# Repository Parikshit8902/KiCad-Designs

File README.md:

# KiCad-Designs
Here's some of my design prototypes, which I designed with the help of KiCad.
These designs have a schematic file as well as a PCB-Design file.

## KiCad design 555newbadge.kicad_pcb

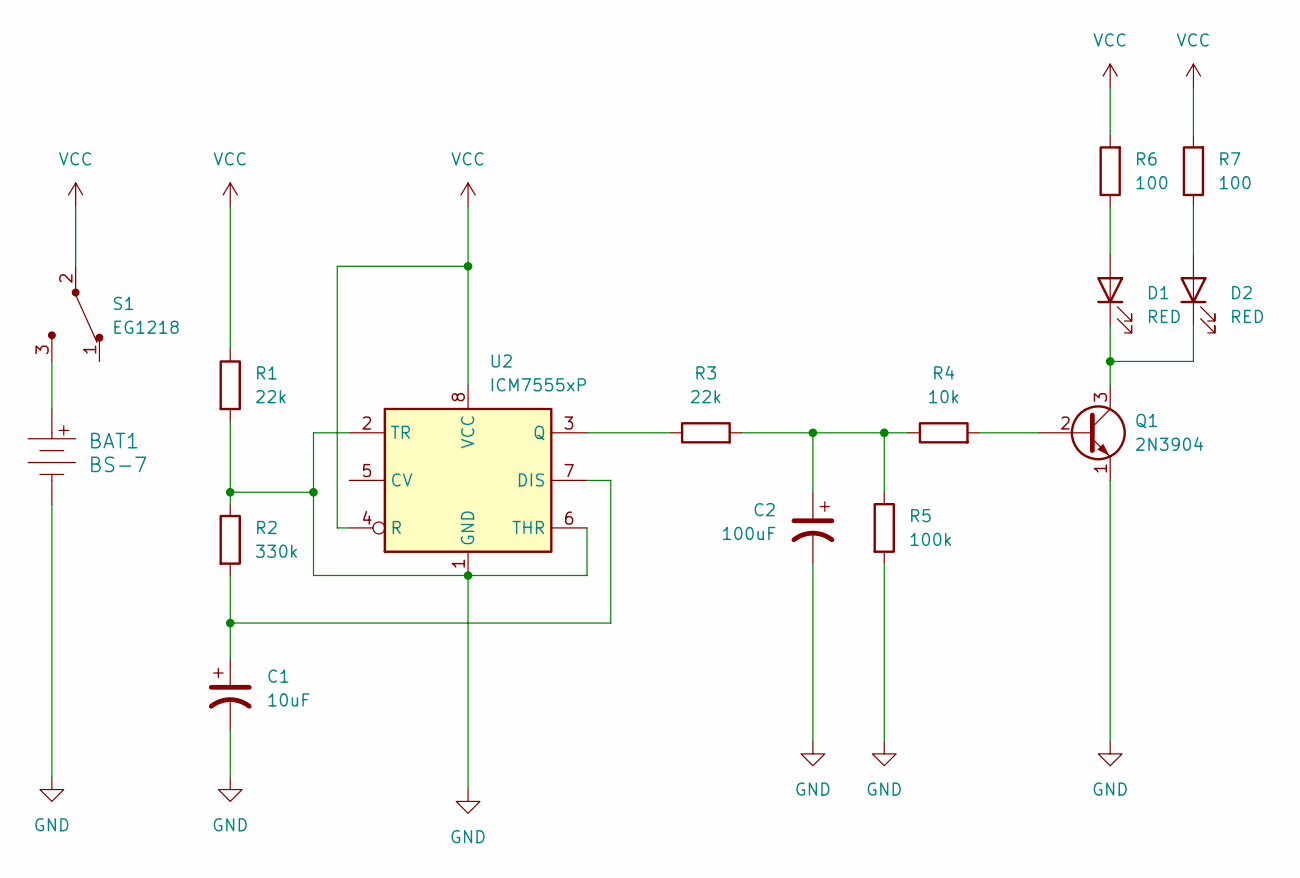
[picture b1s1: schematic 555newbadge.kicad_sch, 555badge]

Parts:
BAT1: BS-7; Battery_Holder_Coin_2032_BS-7; MPN BS-7; Digi-Key_PN BS-7-ND
C1: 10uF; CP_Radial_D5.0mm_P2.00mm
C2: 100uF; CP_Radial_D6.3mm_P2.50mm
D1, D2: RED; LED_D3.0mm
Q1: 2N3904; TO-92-3
R1, R3: 22k; R_Axial_DIN0207_L6.3mm_D2.5mm_P7.62mm_Horizontal
R2: 330k; R_Axial_DIN0207_L6.3mm_D2.5mm_P7.62mm_Horizontal
R4: 10k; R_Axial_DIN0207_L6.3mm_D2.5mm_P7.62mm_Horizontal
R5: 100k; R_Axial_DIN0207_L6.3mm_D2.5mm_P7.62mm_Horizontal
R6, R7: 100; R_Axial_DIN0207_L6.3mm_D2.5mm_P7.62mm_Horizontal
S1: EG1218; Switch_Slide_11.6x4mm_EG1218; MPN EG1218; Digi-Key_PN EG1903-ND
U2: ICM7555xP; DIP-8_W7.62mm

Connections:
GND: BAT1.Neg, C1.2, C2.2, Q1.1 (E), R1.2, R2.1, R5.2, U2.1 (GND), U2.2 (TR), U2.6 (THR)
unnamed: BAT1.Pos, S1.3
unnamed: C2.1, R3.2, R4.1, R5.1
unnamed: D1.2 (A), R6.1
unnamed: D1.1 (K), D2.1 (K), Q1.3 (C)
unnamed: D2.2 (A), R7.1
unnamed: Q1.2 (B), R4.2
unnamed: C1.1, R2.2, U2.7 (DIS)
unnamed: R3.1, U2.3 (Q)
VCC: R1.1, R6.2, R7.2, S1.2, U2.4 (R), U2.8 (VCC)

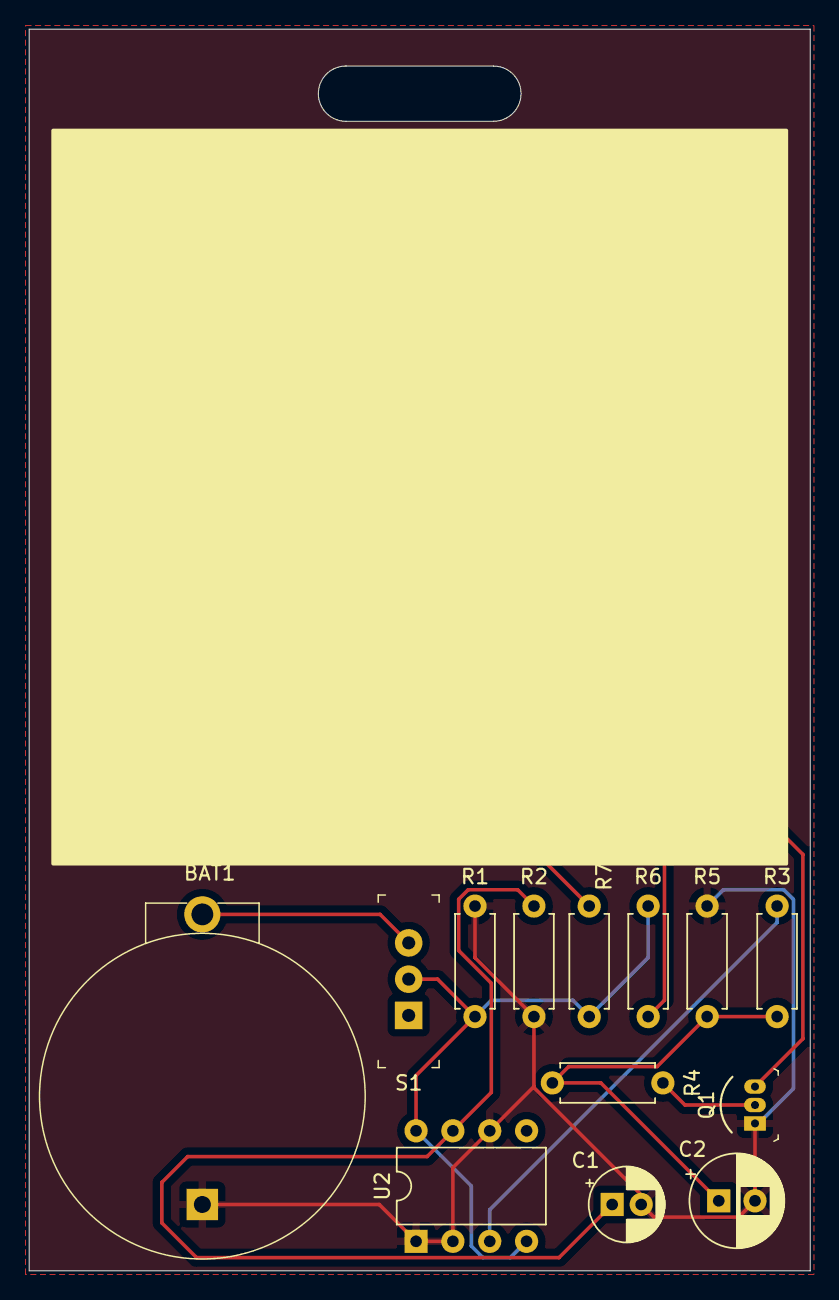
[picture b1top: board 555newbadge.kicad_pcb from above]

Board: 2 copper layers, 53.8 x 85.6 mm, 15 parts (0 on the bottom side), 10 nets.

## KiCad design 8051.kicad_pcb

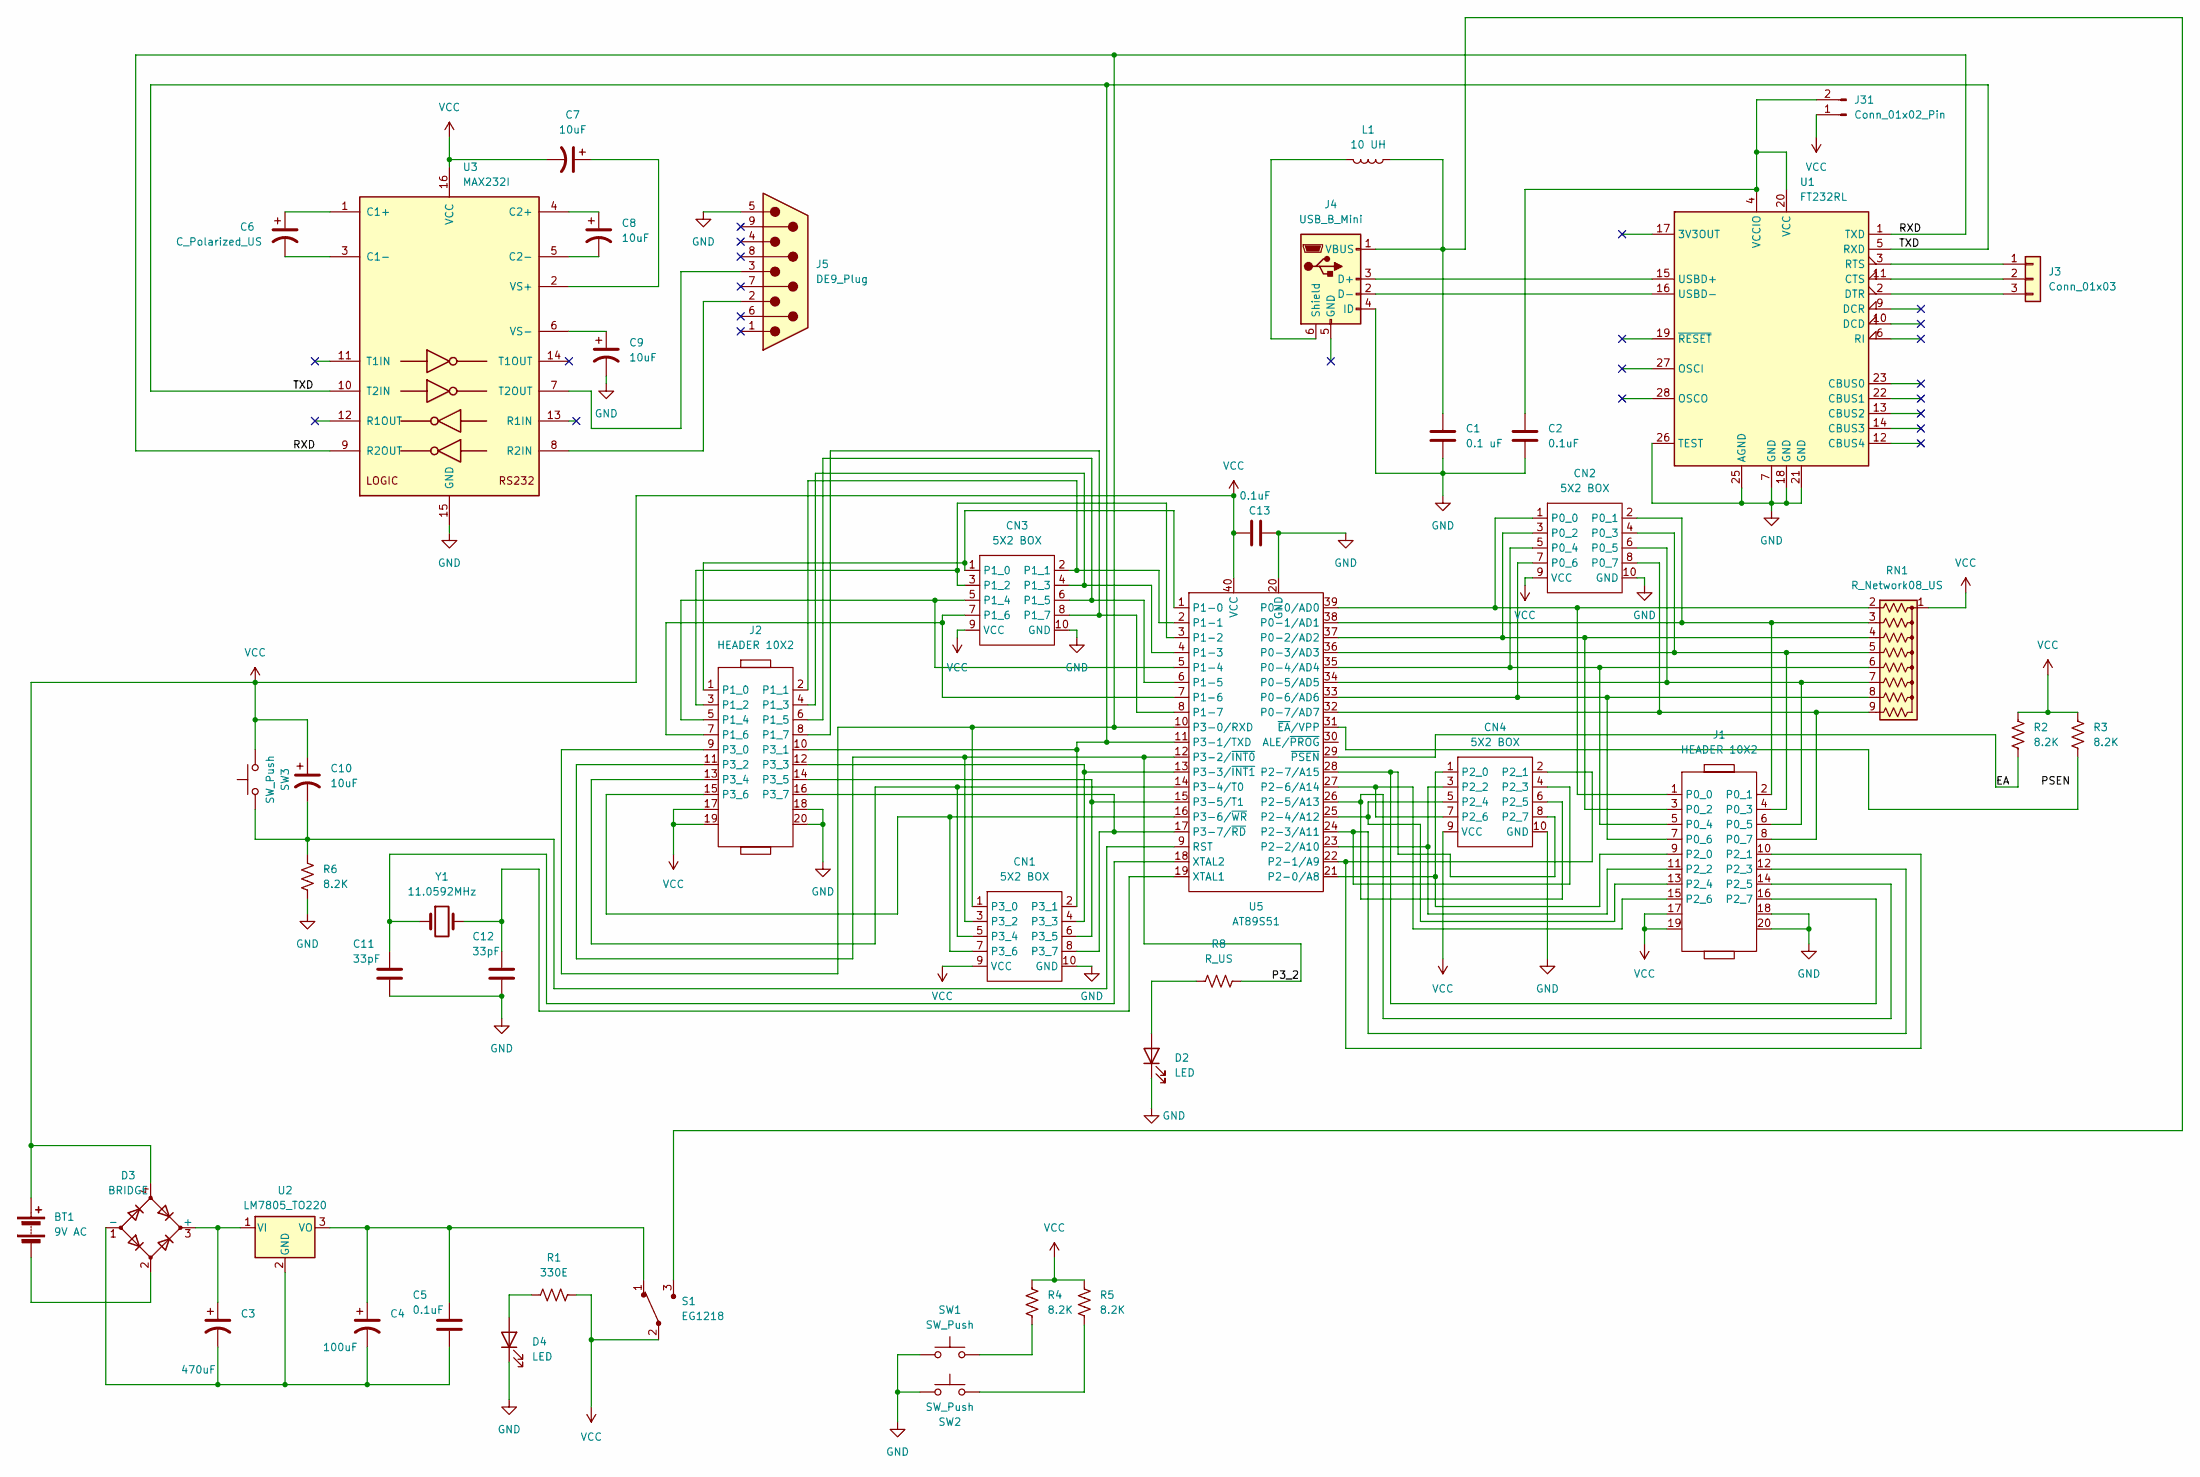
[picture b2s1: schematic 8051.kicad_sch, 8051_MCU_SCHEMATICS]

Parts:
BT1: 9V AC; Battery_Panasonic_CR1025-VSK_Vertical_CircularHoles
C1: 0.1 uF; CP_Radial_D8.0mm_P2.50mm
C2, C13: 0.1uF; CP_Radial_D8.0mm_P2.50mm
C3: 470uF; CP_Radial_D6.3mm_P2.50mm
C4: 100uF; CP_Radial_D6.3mm_P2.50mm
C5: 0.1uF; CP_Radial_D5.0mm_P2.00mm
C6: C_Polarized_US; CP_Radial_D6.3mm_P2.50mm
C7, C8, C9, C10: 10uF; CP_Radial_D6.3mm_P2.50mm
C11, C12: 33pF; CP_Radial_D5.0mm_P2.00mm
CN1, CN2, CN3, CN4: 5X2 BOX; PinHeader_2x05_P2.54mm_Vertical
D2, D4: LED; LED_D3.0mm
D3: BRIDGE; Diode_Bridge_Vishay_KBU
J1, J2: HEADER 10X2; PinHeader_2x10_P2.54mm_Vertical
J3: Conn_01x03; PinHeader_1x03_P2.54mm_Vertical
J4: USB_B_Mini; USB_B_Amphenol_MUSB-D511_Vertical_Rugged
J5: DE9_Plug; DSUB-9_Female_Horizontal_P2.77x2.84mm_EdgePinOffset7.70mm_H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
J31: Conn_01x02_Pin; PinHeader_1x02_P2.54mm_Vertical
L1: 10 UH; L_6.3x6.3_H3
R1: 330E; R_Axial_DIN0207_L6.3mm_D2.5mm_P7.62mm_Horizontal
R2, R3, R4, R5, R6: 8.2K; R_Axial_DIN0207_L6.3mm_D2.5mm_P15.24mm_Horizontal
R8: R_US; R_Axial_DIN0207_L6.3mm_D2.5mm_P2.54mm_Vertical
RN1: R_Network08_US; R_Array_SIP9
S1: EG1218; Switch_Slide_11.6x4mm_EG1218; MPN EG1218; Digi-Key_PN EG1903-ND
SW1, SW2, SW3: SW_Push; SW_PUSH_6mm_H4.3mm
U1: FT232RL; SSOP-28_5.3x10.2mm_P0.65mm
U2: LM7805_TO220; TO-220-3_Vertical
U3: MAX232I; MAX232
U5: AT89S51
Y1: 11.0592MHz; Crystal_HC49-U_Vertical

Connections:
/EA: R2.2, U5.29 (~PSEN)
/P3_2: CN1.3 (P3_2), J2.11 (P3_2), R8.2, U5.12 (P3-2/~INT0)
/RXD: CN1.1 (P3_0), J2.9 (P3_0), U1.1 (TXD), U3.9 (R2OUT), U5.10 (P3-0/RXD)
/TXD: CN1.2 (P3_1), J2.10 (P3_1), U1.5 (RXD), U3.10 (T2IN), U5.11 (P3-1/TXD)
GND: C1.2, C2.2, C9.2, C11.2, C12.2, C13.2, CN1.10 (GND), CN2.10 (GND), CN3.10 (GND), CN4.10 (GND), D2.1 (K), D4.1 (K), J1.18, J1.20, J2.18, J2.20, J4.4 (ID), J5.5, R6.2, SW1.1, SW2.1, U1.7 (GND), U1.18 (GND), U1.21 (GND), U1.25 (AGND), U1.26 (TEST), U3.15 (GND), U5.20 (GND)
unnamed: BT1.2 (-), D3.2
unnamed: CN1.4 (P3_3), J2.12 (P3_3), U5.13 (P3-3/~INT1)
unnamed: CN1.5 (P3_4), J2.13 (P3_4), U5.14 (P3-4/T0)
unnamed: CN1.6 (P3_5), J2.14 (P3_5), U5.15 (P3-5/T1)
unnamed: CN1.7 (P3_6), J2.15 (P3_6), U5.16 (P3-6/~WR)
unnamed: CN1.8 (P3_7), J2.16 (P3_7), U5.17 (P3-7/~RD)
unnamed: CN2.1 (P0_0), J1.1 (P0_0), RN1.2 (R1), U5.39 (P0-0/AD0)
unnamed: CN2.2 (P0_1), J1.2 (P0_1), RN1.3 (R2), U5.38 (P0-1/AD1)
unnamed: CN2.3 (P0_2), J1.3 (P0_2), RN1.4 (R3), U5.37 (P0-2/AD2)
unnamed: CN2.4 (P0_3), J1.4 (P0_3), RN1.5 (R4), U5.36 (P0-3/AD3)
unnamed: CN2.5 (P0_4), J1.5 (P0_4), RN1.6 (R5), U5.35 (P0-4/AD4)
unnamed: CN2.6 (P0_5), J1.6 (P0_5), RN1.7 (R6), U5.34 (P0-5/AD5)
unnamed: CN2.7 (P0_6), J1.7 (P0_6), RN1.8 (R7), U5.33 (P0-6/AD6)
unnamed: CN2.8 (P0_7), J1.8 (P0_7), RN1.9 (R8), U5.32 (P0-7/AD7)
unnamed: CN3.1 (P1_0), J2.1 (P1_0), U5.1 (P1-0)
unnamed: CN3.2 (P1_1), J2.2 (P1_1), U5.2 (P1-1)
unnamed: CN3.3 (P1_2), J2.3 (P1_2), U5.3 (P1-2)
unnamed: CN3.4 (P1_3), J2.4 (P1_3), U5.4 (P1-3)
unnamed: CN3.5 (P1_4), J2.5 (P1_4), U5.5 (P1-4)
unnamed: CN3.6 (P1_5), J2.6 (P1_5), U5.6 (P1-5)
unnamed: CN3.7 (P1_6), J2.7 (P1_6), U5.7 (P1-6)
unnamed: CN3.8 (P1_7), J2.8 (P1_7), U5.8 (P1-7)
unnamed: CN4.1 (P2_0), J1.9 (P2_0), U5.21 (P2-0/A8)
unnamed: CN4.2 (P2_1), J1.10 (P2_1), U5.22 (P2-1/A9)
unnamed: CN4.3 (P2_2), J1.11 (P2_2), U5.23 (P2-2/A10)
unnamed: CN4.4 (P2_3), J1.12 (P2_3), U5.24 (P2-3/A11)
unnamed: CN4.5 (P2_4), J1.13 (P2_4), U5.25 (P2-4/A12)
unnamed: CN4.6 (P2_5), J1.14 (P2_5), U5.26 (P2-5/A13)
unnamed: CN4.7 (P2_6), J1.15 (P2_6), U5.27 (P2-6/A14)
unnamed: CN4.8 (P2_7), J1.16 (P2_7), U5.28 (P2-7/A15)
unnamed: D2.2 (A), R8.1
unnamed: C3.1, D3.3 (+), U2.1 (VI)
unnamed: C3.2, C4.2, C5.2, D3.1 (-), U2.2 (GND)
unnamed: D4.2 (A), R1.1
unnamed: J3.1, U1.3 (RTS)
unnamed: J3.2, U1.11 (CTS)
unnamed: J3.3, U1.2 (DTR)
unnamed: J4.3 (D+), U1.15 (USBD+)
unnamed: J4.2 (D-), U1.16 (USBD-)
unnamed: J4.6 (Shield), L1.2
unnamed: C1.1, J4.1 (VBUS), L1.1, S1.3
unnamed: C2.1, J31.2, U1.4 (VCCIO), U1.20 (VCC)
unnamed: R4.2, SW1.2
unnamed: R5.2, SW2.2
unnamed: C4.1, C5.1, S1.1, U2.3 (VO)
unnamed: C6.1, U3.1 (C1+)
unnamed: C6.2, U3.3 (C1-)
unnamed: C8.1, U3.4 (C2+)
unnamed: C8.2, U3.5 (C2-)
unnamed: J5.2, U3.8 (R2IN)
unnamed: J5.3, U3.7 (T2OUT)
unnamed: C7.1, U3.2 (VS+)
unnamed: C9.1, U3.6 (VS-)
unnamed: C10.2, R6.1, SW3.1, U5.9 (RST)
unnamed: C12.1, U5.19 (XTAL1), Y1.2
unnamed: C11.1, U5.18 (XTAL2), Y1.1
unnamed: R3.2, U5.31 (~EA/VPP)
VCC: BT1.1 (+), C7.2, C10.1, C13.1, CN1.9 (VCC), CN2.9 (VCC), CN3.9 (VCC), CN4.9 (VCC), D3.4, J1.17, J1.19, J2.17, J2.19, J31.1, R1.2, R2.1, R3.1, R4.1, R5.1, RN1.1 (common), S1.2, SW3.2, U3.16 (VCC), U5.40 (VCC)

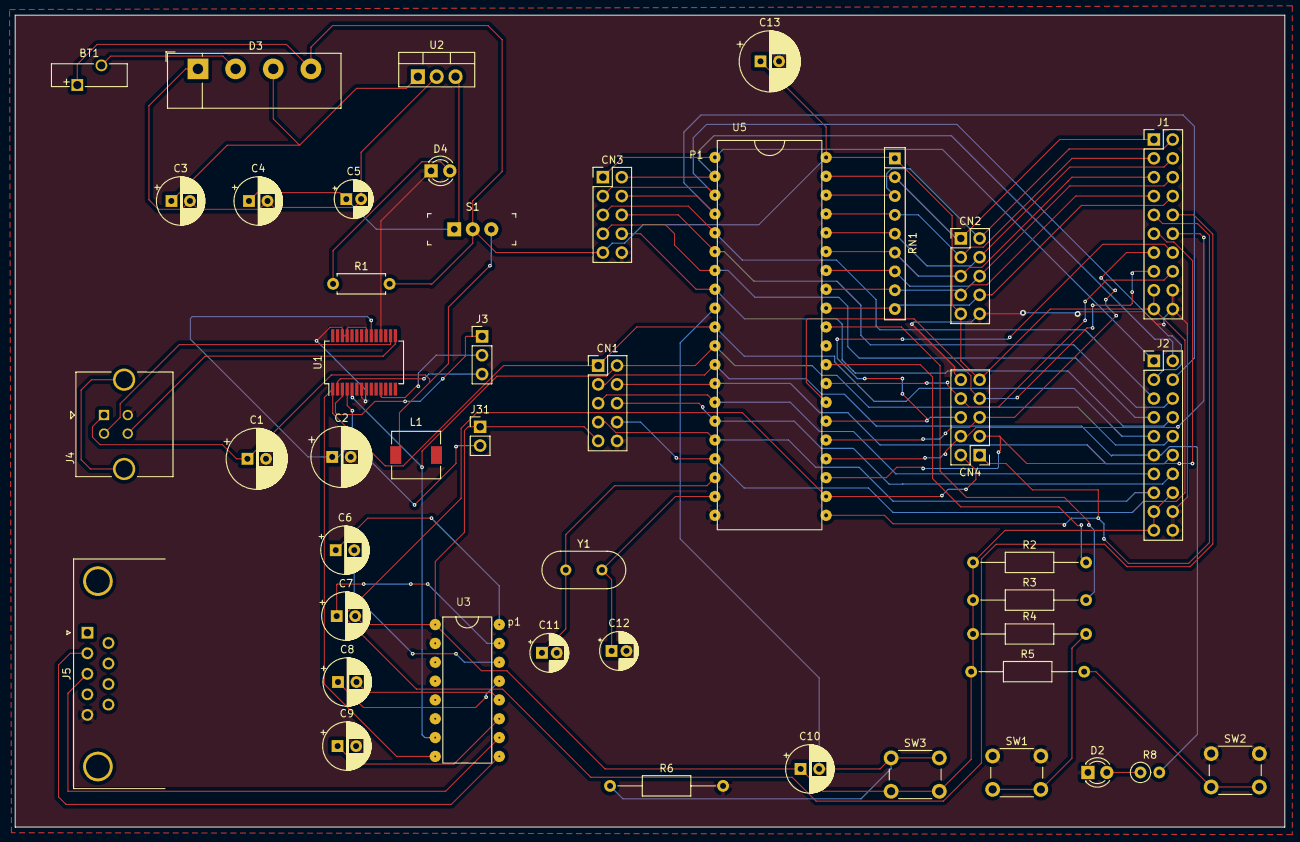
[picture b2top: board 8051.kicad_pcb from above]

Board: 2 copper layers, 171.2 x 109.5 mm, 45 parts (0 on the bottom side), 62 nets.

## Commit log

2023-08-04 Create 8051_MCU

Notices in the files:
555newbadge.kicad_pcb:
creativecommons/licenses/by/4.0
LICENSE: CC BY 4.0
555newbadge.kicad_sch:
creativecommons.org/licenses/by/4.0
